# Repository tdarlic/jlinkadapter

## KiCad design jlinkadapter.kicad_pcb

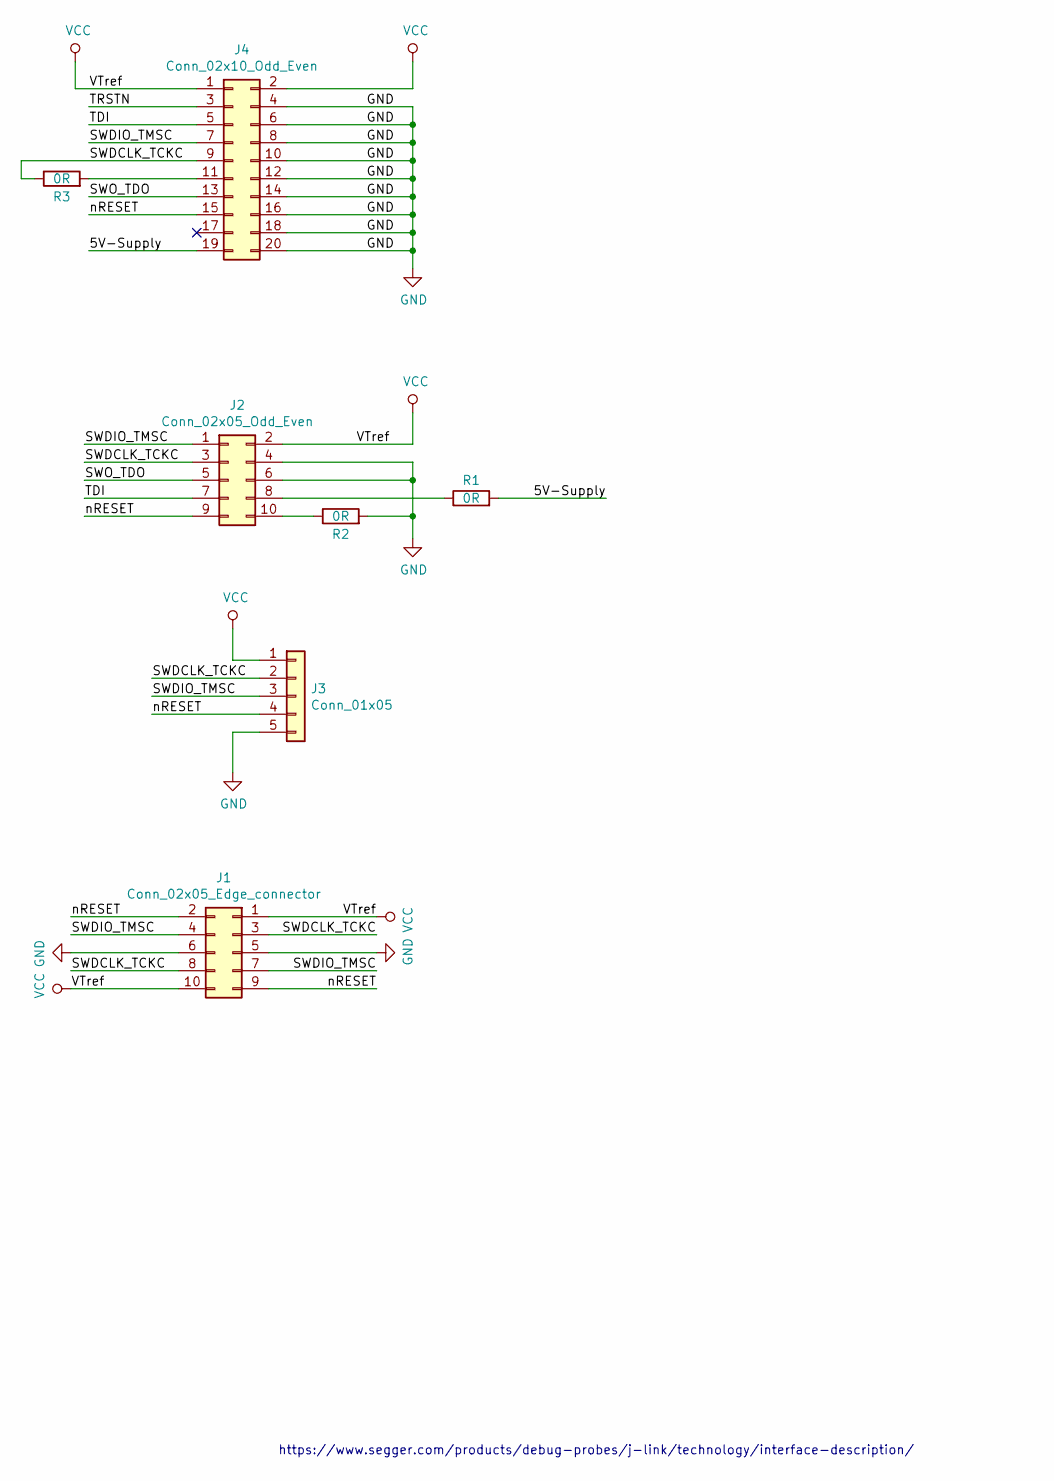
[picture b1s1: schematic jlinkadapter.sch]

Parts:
J1: Conn_02x05_Edge_connector; PCIE-10-TH
J2: Conn_02x05_Odd_Even; IDC-10-SMD-BOARD
J3: Conn_01x05; PinHeader_1x05_P2.54mm_Horizontal
J4: Conn_02x10_Odd_Even; IDC-Header_2x10_P2.54mm_Vertical
R1, R2, R3: 0R; R_1206_3216Metric_Pad1.42x1.75mm_HandSolder

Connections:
/5V-Supply: J4.19, R1.2
/SWDCLK_TCKC: J1.3, J1.8, J2.3, J3.2, J4.9, R3.1
/SWDIO_TMSC: J1.4, J1.7, J2.1, J3.3, J4.7
/SWO_TDO: J2.5, J4.13
/TDI: J2.7, J4.5
/TRSTN: J4.3
/nRESET: J1.2, J1.9, J2.9, J3.4, J4.15
GND: J1.5, J1.6, J2.4, J2.6, J3.5, J4.4, J4.6, J4.8, J4.10, J4.12, J4.14, J4.16, J4.18, J4.20, R2.2
unnamed: J2.8, R1.1
unnamed: J2.10, R2.1
unnamed: J4.11, R3.2
VCC: J1.1, J1.10, J2.2, J3.1, J4.1, J4.2

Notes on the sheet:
https://www.segger.com/products/debug-probes/j-link/technology/interface-description/

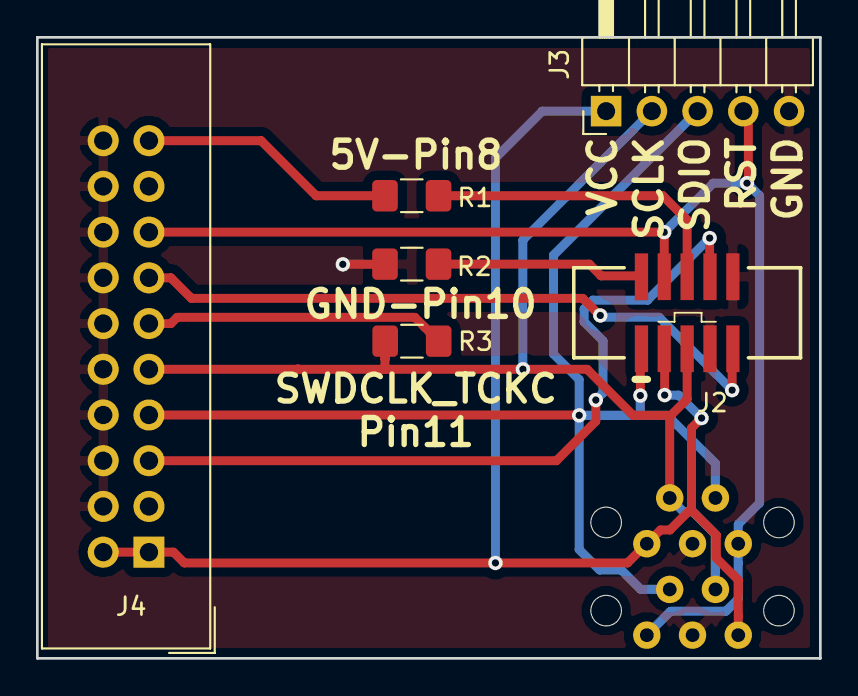
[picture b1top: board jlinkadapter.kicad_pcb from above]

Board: 2 copper layers, 43.5 x 34.5 mm, 7 parts (1 on the bottom side), 11 nets.

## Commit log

2018-12-18 Small fixes, exporting gerbers for fab
2018-12-20 Fixing smaller changes in footprint, adding wider holes on edge connector
